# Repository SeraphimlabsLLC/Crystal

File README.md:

# Crystal
ESP32-C3 Wifi adapter for embedded projects

Tested to work with DCC-EX 5.0 using Expressif AT Firmware 3.2 in STA mode. AP mode works but may still have undiscovered issues.

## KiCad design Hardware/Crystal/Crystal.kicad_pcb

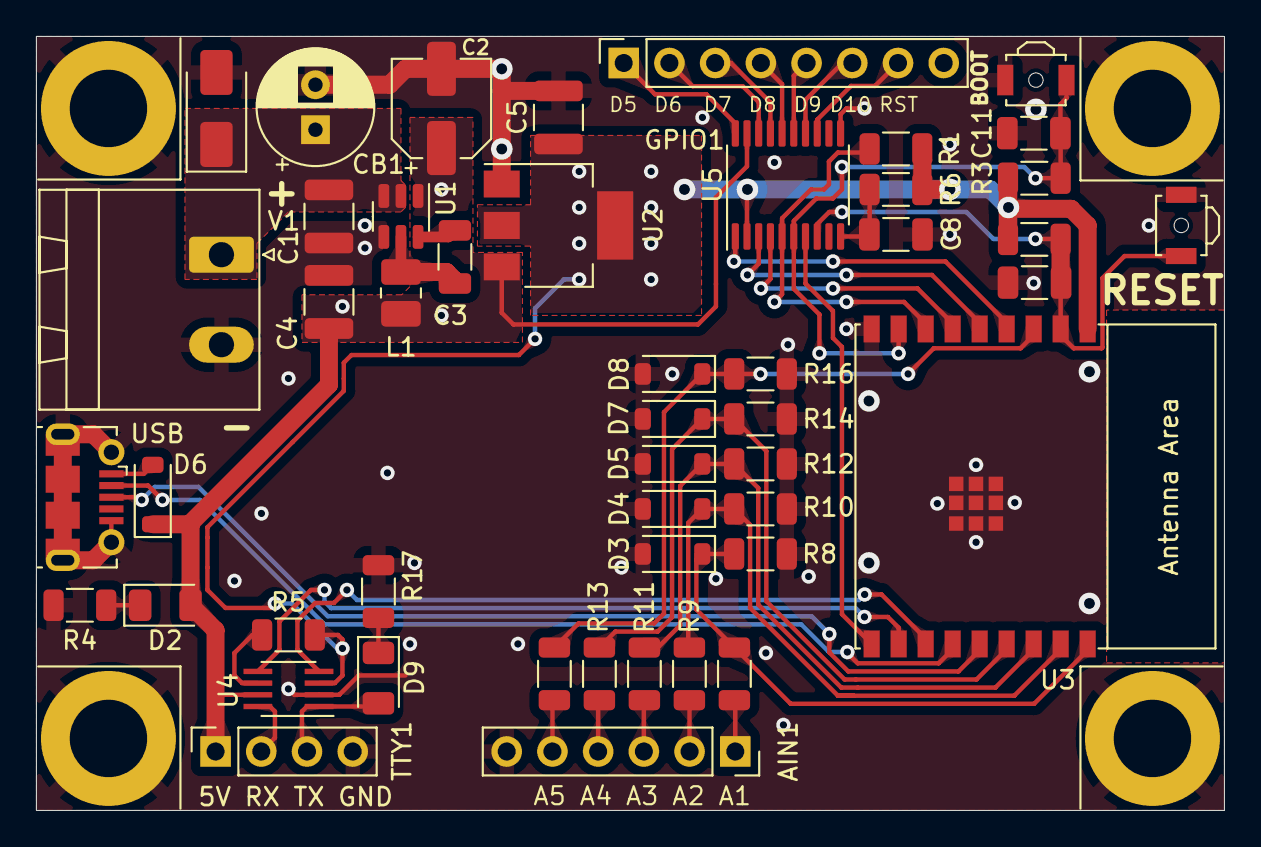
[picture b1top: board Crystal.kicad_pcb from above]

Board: 2 copper layers, 66.0 x 43.0 mm, 48 parts (0 on the bottom side), 41 nets.

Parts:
AIN1: Conn_01x06; PinSocket_1x06_P2.54mm_Vertical
BOOT1: SW_Push; SW_SPST_B3U-3000P-B
C1, C4, C5: 10uF; C_1210_3225Metric
C2: 22uF; CP_Elec_5x5.3
C3: 0.1uF; C_1206_3216Metric
C8, C10, C11: 1uf; C_1206_3216Metric
CB1: 100uF; CP_Radial_D6.3mm_P2.50mm
D1: SMAJ18CA; D_SMA
D2: Red; LED_1206_3216Metric
D3, D4, D5, D7, D8: 3.3v; D_SOD-123
D6: PMEG2005EGWX; D_SOD-123
D9: Blue; LED_1206_3216Metric
GPIO1: Conn_01x08; PinSocket_1x08_P2.54mm_Vertical
J1: USB_B_Micro; USB_Micro-B_Molex-105017-0001
L1: 4.7uH; L_1008_2520Metric_Pad1.43x2.20mm_HandSolder
R1, R5, R6: 47k; R_1206_3216Metric
R2, R3: 10k; R_1206_3216Metric
R4, R17: 1k; R_1206_3216Metric
R7, R9, R11, R13, R15: 11k; R_1206_3216Metric
R8, R10, R12, R14, R16: 22k; R_1206_3216Metric
RESET1: SW_Push; SW_SPST_B3U-3000P-B
TTY1: Conn_01x04; PinSocket_1x04_P2.54mm_Vertical
U1: AP63205WU; TSOT-23-6
U2: NCP1117-3.3_SOT223; SOT-223-3_TabPin2
U3: ESP32-C3-WROOM-02
U4: TXS0102DCT; SSOP-8_2.95x2.8mm_P0.65mm
U5: TXS0108EPW; TSSOP-20_4.4x6.5mm_P0.65mm
V1: Conn_01x02; PhoenixContact_MSTBA_2,5_2-G_1x02_P5.00mm_Horizontal

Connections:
+3.3V: C5.1, R1.1, R2.1, R3.1, R5.2, R6.2, U2.2 (VO), U3.1 (3V3), U4.3 (VCCA), U5.2 (VCCA)
+5V: C2.1, C4.1, D2.2 (A), D6.1 (K), L1.2, TTY1.1, U1.1 (FB), U2.3 (VI), U4.7 (VCCB), U5.19 (VCCB)
+12V: C1.1, CB1.1, D1.1 (A1), U1.2 (EN), U1.3 (IN), V1.1
/AIN1: D3.1 (K), R7.1, R8.2, U3.18 (GPIO0/ADC1_CH0/XTAL_32K_P)
/AIN2: D4.1 (K), R9.1, R10.2, U3.17 (GPIO1/ADC1_CH1/XTAL_32K_N)
/AIN3: D5.1 (K), R11.1, R12.2, U3.16 (GPIO2/ADC1_CH2)
/AIN4: D7.1 (K), R13.1, R14.2, U3.15 (GPIO3/ADC1_CH3)
/AIN5: D8.1 (K), R15.1, R16.2, U3.3 (GPIO4/ADC1_CH4)
/GPIO5: U3.4 (GPIO5/ADC2_CH0), U5.1 (A1)
/GPIO6: U3.5 (GPIO6), U5.3 (A2)
/GPIO7: U3.6 (GPIO7), U5.4 (A3)
/GPIO8: R1.2, U3.7 (GPIO8), U5.5 (A4)
/GPIO9: BOOT1.2, C11.2, R3.2, U3.8 (GPIO9), U5.6 (A5)
/GPIO10: U3.10 (GPIO10), U5.7 (A6)
/RESET: C10.2, R2.2, RESET1.2, U3.2 (EN/CHIP_PU), U5.8 (A7)
/RXD: U3.11 (GPIO20/U0RXD), U4.5 (A1)
/TXD: U3.12 (GPIO21/U0TXD), U4.4 (A2)
/USB_D+: J1.3 (D+), U3.14 (GPIO19/USB_D+)
/USB_D-: J1.2 (D-), U3.13 (GPIO18/USB_D-)
GND: AIN1.6, BOOT1.1, C1.2, C2.2, C4.2, C5.2, C8.2, C10.1, C11.1, CB1.2, D1.2 (A2), D3.2 (A), D4.2 (A), D5.2 (A), D7.2 (A), D8.2 (A), J1.5 (GND), J1.6 (Shield), R4.1, R8.1, R10.1, R12.1, R14.1, R16.1, R17.2, RESET1.1, TTY1.4, U1.4 (GND), U2.1 (GND), U3.9 (GND), U3.19 (GND), U4.2 (GND), U5.11 (GND), V1.2
unnamed: AIN1.1, R7.2
unnamed: AIN1.2, R9.2
unnamed: AIN1.3, R11.2
unnamed: AIN1.4, R13.2
unnamed: AIN1.5, R15.2
unnamed: D2.1 (K), R4.2
unnamed: D6.2 (A), J1.1 (VBUS)
unnamed: D9.2 (A), TTY1.3, U4.1 (B2)
unnamed: D9.1 (K), R17.1
unnamed: GPIO1.1, U5.20 (B1)
unnamed: GPIO1.2, U5.18 (B2)
unnamed: GPIO1.3, U5.17 (B3)
unnamed: GPIO1.4, U5.16 (B4)
unnamed: GPIO1.5, U5.15 (B5)
unnamed: GPIO1.6, U5.14 (B6)
unnamed: GPIO1.7, U5.13 (B7)
unnamed: TTY1.2, U4.8 (B1)
unnamed: C3.1, U1.6 (BST)
unnamed: C3.2, L1.1, U1.5 (SW)
unnamed: R5.1, U4.6 (OE)
unnamed: C8.1, R6.1, U5.10 (OE)

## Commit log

2023-07-30 Completed schematic with BOM and PCB layout.
2023-07-30 Fixing missing file
2023-08-20 Revised L1 for possible 2A output, cleaner fill zones
2023-08-21 Added note about VIN plug, BOM cleanup.
2023-09-28 First build using ESP AT Firmware 3.2
2023-09-30 Update README.md
    Add testing results
2023-11-26 Checkpoint
2023-12-17 Final cleanup, added tags for JLCPCB Fabrication
2023-12-18 Swap TX and RX pins on COM port, populate PCBA data in KiCad
2023-12-18 Further board cleanup
2023-12-31 Changed mounting holes to be drilled and plated instead of milled.
2023-12-31 Updated notes on schematic
2024-01-13 PCB Revision for 5mm power plug to match EX-8874
2024-01-13 Further PCB revision to use MLCC caps in the 5v regulator for better smoothing and space utilization
2024-01-13 Added Shield version of Crystal, and support for Wifinina on both versions.
2024-01-30 BOM fix, replace NCP1117 with TLV1117 and add Arduino stacking headers
